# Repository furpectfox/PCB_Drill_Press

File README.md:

# PCB Drill Press

## [Schematic](Motor_Driver/schematic.pdf)

*The PCB layout is designed to make the circuit as easy to solder on a perfboard as possible.*

## Finish

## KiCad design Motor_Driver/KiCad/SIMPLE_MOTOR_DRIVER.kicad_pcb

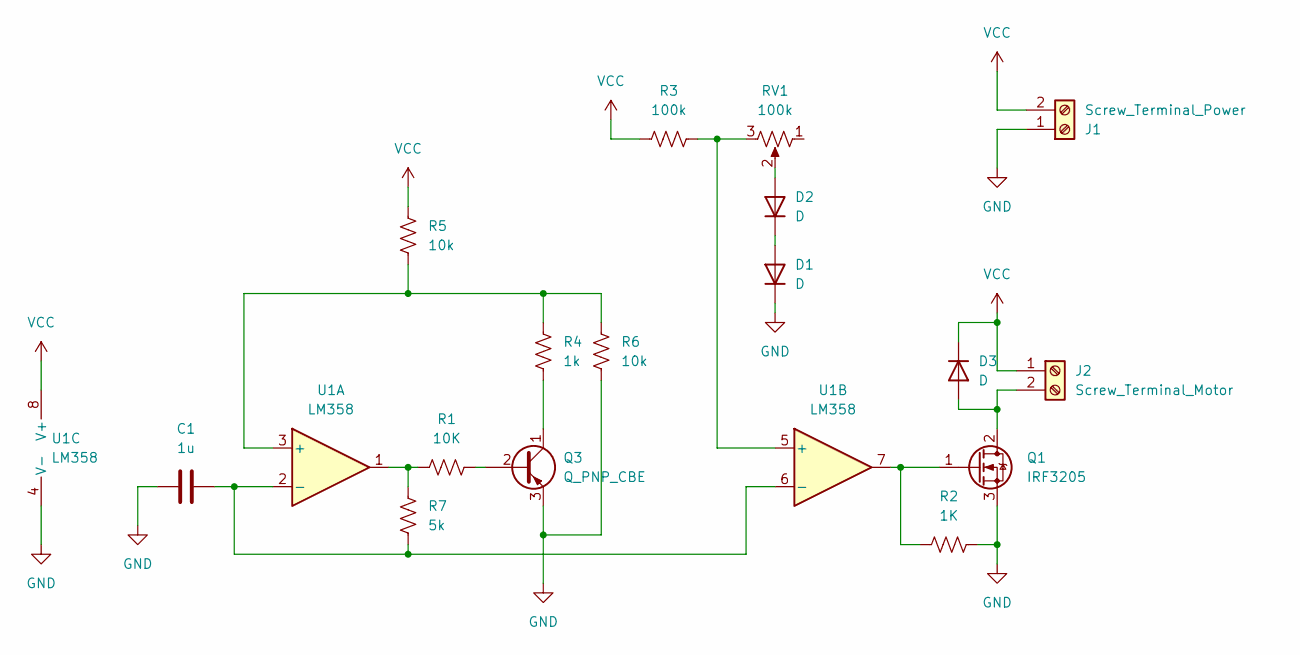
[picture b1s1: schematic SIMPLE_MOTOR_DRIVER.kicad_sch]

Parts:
C1: 1u; C_Disc_D5.1mm_W3.2mm_P5.00mm
D1: D; D_DO-35_SOD27_P7.62mm_Horizontal
D2: D; D_DO-35_SOD27_P2.54mm_Vertical_KathodeUp
D3: D; D_DO-35_SOD27_P5.08mm_Vertical_KathodeUp
J1: Screw_Terminal_Power; TerminalBlock_Altech_AK300-2_P5.00mm
J2: Screw_Terminal_Motor; TerminalBlock_Altech_AK300-2_P5.00mm
Q1: IRF3205; TO-220-3_Vertical
Q3: Q_PNP_CBE; TO-92_Inline_Wide
R1: 10K; R_Axial_DIN0207_L6.3mm_D2.5mm_P5.08mm_Vertical
R2: 1K; R_Axial_DIN0207_L6.3mm_D2.5mm_P5.08mm_Vertical
R3: 100k; R_Axial_DIN0207_L6.3mm_D2.5mm_P7.62mm_Horizontal
R4: 1k; R_Axial_DIN0207_L6.3mm_D2.5mm_P5.08mm_Vertical
R5: 10k; R_Axial_DIN0207_L6.3mm_D2.5mm_P10.16mm_Horizontal
R6: 10k; R_Axial_DIN0207_L6.3mm_D2.5mm_P7.62mm_Horizontal
R7: 5k; R_Axial_DIN0207_L6.3mm_D2.5mm_P2.54mm_Vertical
RV1: 100k; PinHeader_1x03_P2.54mm_Vertical
U1: LM358; DIP-8_W7.62mm

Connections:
GND: C1.1, D1.1 (K), J1.1, Q1.3 (S), Q3.3 (E), R2.2, R6.1, U1.4 (V-)
unnamed: D1.2 (A), D2.1 (K)
unnamed: D2.2 (A), RV1.2
unnamed: D3.2 (A), J2.2, Q1.2 (D)
unnamed: Q1.1 (G), R2.1, U1.7
unnamed: Q3.2 (B), R1.2
unnamed: Q3.1 (C), R4.1
unnamed: R1.1, R7.1, U1.1
unnamed: R4.2, R5.1, R6.2, U1.3 (+)
unnamed: C1.2, R7.2, U1.2 (-), U1.6 (-)
unnamed: R3.2, RV1.3, U1.5 (+)
VCC: D3.1 (K), J1.2, J2.1, R3.1, R5.2, U1.8 (V+)

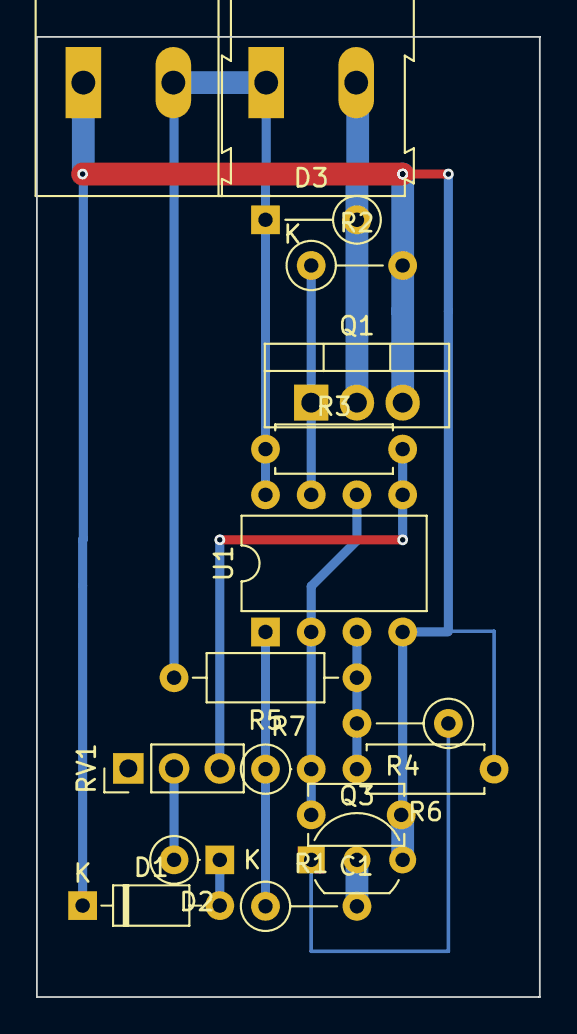
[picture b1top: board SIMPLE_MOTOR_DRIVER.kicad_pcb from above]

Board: 2 copper layers, 27.9 x 53.3 mm, 17 parts (0 on the bottom side), 12 nets.

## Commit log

2024-07-18 Create schematic and pcb_layout files
2025-03-03 upload CAD files and update schematic
2025-03-09 add KiCad folder
2025-03-11 Update KiCad files
